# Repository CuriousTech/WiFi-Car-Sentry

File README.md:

# WiFi Car Sentry
Low power car monitor and control system  
  
Revision 2  
  
Using the ESP07, it connects with the home WiFi to report information on timer using DeepSleep.  Remember to remove the red LED on the ESP to reduce current.  This new revision uses a switching regulator for the lowest current possible.  It uses about 25mA on, and 39µA in sleep at 12.5V.  
  
I/O peripherals:  
  OLED (optional for temporary display)  
  DHT22 for temperature and Rh  
  0-17V analog voltage reading  
  2x 1-40V digital input (for sensing if something is on)  
  3x sink inputs (alarm or sensor)  
  3 sink outputs for controlling relays, etc (the bom has 7.6A MOSFETs)  
  Plus extra O/I for GPS or other sensors. The outputs can be used to switch them off for more power saving.

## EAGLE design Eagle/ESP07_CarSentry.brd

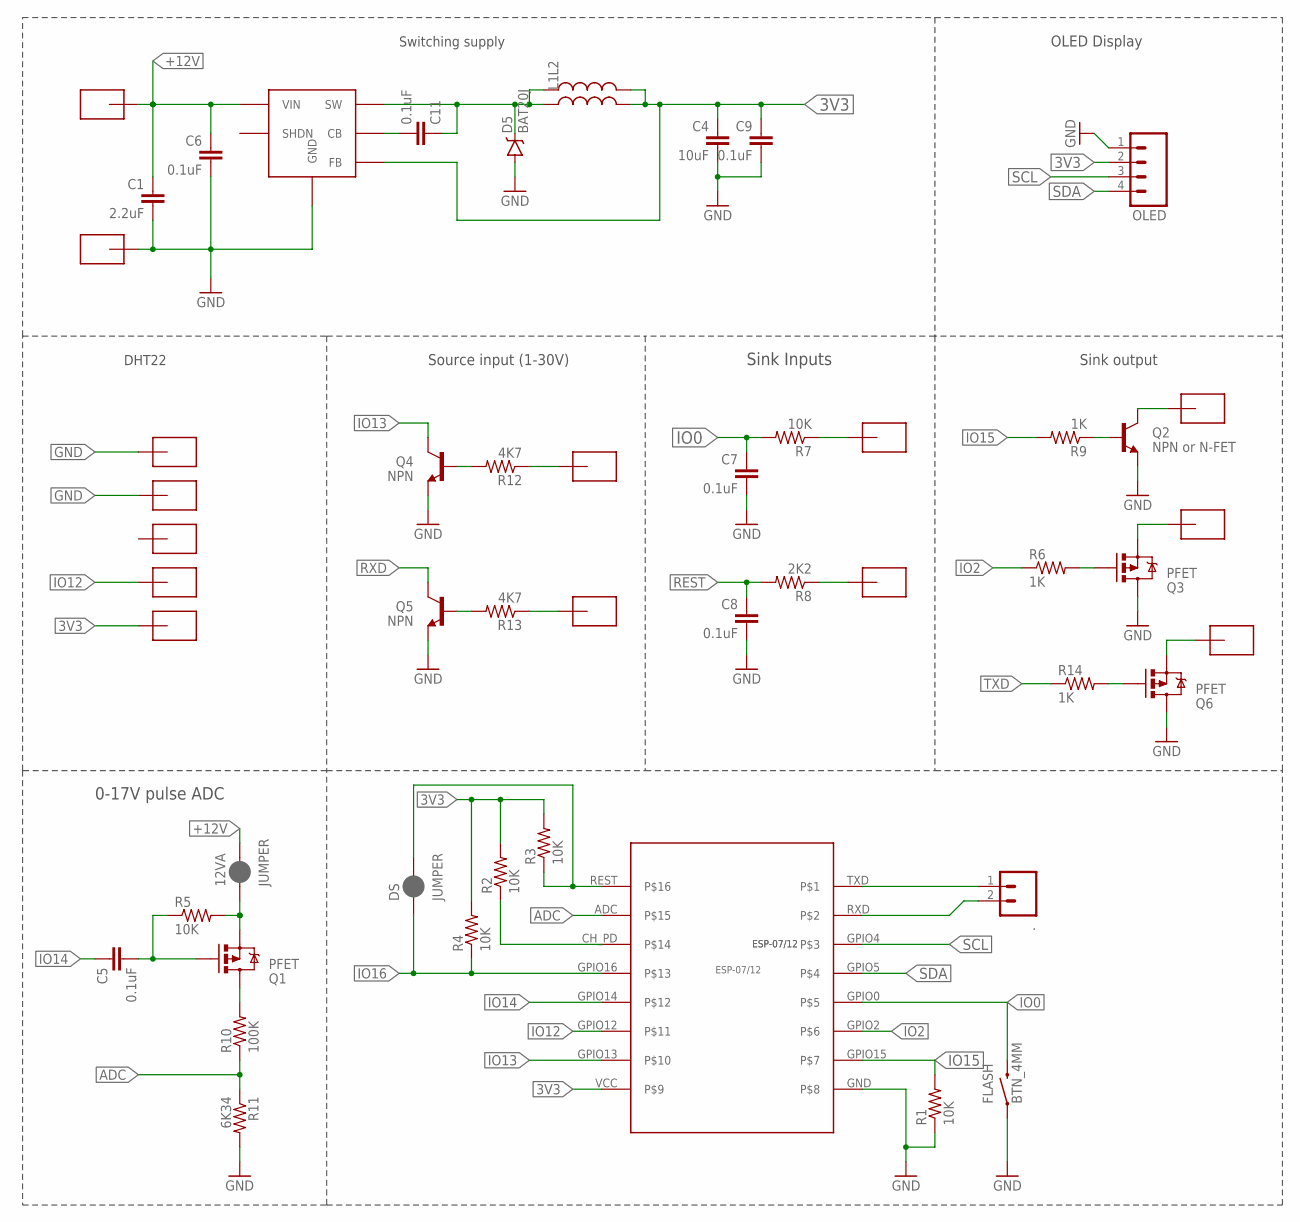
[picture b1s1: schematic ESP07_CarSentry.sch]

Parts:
12VA: JUMPER; PAD-JUMPER-2-NC_BY_PASTE_YES_SILK
.: M02PTH; 1X02
C1: 2.2uF; 0805-CAP
C4: 10uF; 0805-CAP
C5, C6, C7, C8, C9, C11: 0.1uF; 0805-CAP
D5: BAT20J; SOD-323
DS: JUMPER; PAD-JUMPER-2-NC_BY_PASTE_YES_SILK
FLASH: BTN_4MM
L1, L2: INDUCTOR0805; 0805
OLED: M04LOCK; 1X04_LOCK
Q1, Q3, Q6: PFET; SOT23-3
Q2: NPN or N-FET; SOT23-3
Q4, Q5: NPN; SOT23-3
R1, R2, R3, R4, R5, R7: 10K; 0805
R6, R9, R14: 1K; 0805
R8: 2K2; 0805
R10: 100K; 0805
R11: 6K34; 0805
R12, R13: 4K7; 0805
U$1: ESP-07/12
U$2, U$3, U$4, U$5, U$6, U$7, U$8, U$9, U$10, U$11, U$12, U$13, U$14, U$16: SMD-PAD1
VREG1: LMR16006YQ3DDCRQ1; SOT-23-6

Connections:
3V3: C4.1, C9.1, L1.2, L2.2, OLED.2, R2.2, R3.2, R4.2, U$1.VCC, U$4.>NAME, VREG1.3 (FB)
+12V: 12VA.2, C1.1, C6.1, U$16.>NAME, VREG1.5 (VIN)
ADC: R10.1, R11.1, U$1.ADC
ADCHI: 12VA.1, Q1.2 (S), R5.2
GND: C1.2, C4.2, C6.2, C7.2, C8.2, C9.2, D5.A, FLASH.1, OLED.1, Q2.2 (E), Q3.3 (D), Q4.2 (E), Q5.2 (E), Q6.3 (D), R1.1, R11.2, U$1.GND, U$6.>NAME, U$8.>NAME, U$11.>NAME, VREG1.2 (GND)
IO0: C7.1, FLASH.2, R7.2, U$1.GPIO0
IO2: R6.1, U$1.GPIO2
IO12: U$1.GPIO12, U$5.>NAME
IO13: Q4.3 (C), U$1.GPIO13
IO14: C5.1, U$1.GPIO14
IO15: R1.2, R9.2, U$1.GPIO15
IO16: DS.1, R4.1, U$1.GPIO16
unnamed: Q1.3 (D), R10.2
unnamed: Q3.1 (G), R6.2
unnamed: C5.2, Q1.1 (G), R5.1
unnamed: Q3.2 (S), U$9.>NAME
unnamed: R7.1, U$14.>NAME
unnamed: Q2.1 (B), R9.1
unnamed: Q2.3 (C), U$3.>NAME
unnamed: R8.1, U$12.>NAME
unnamed: Q4.1 (B), R12.2
unnamed: R12.1, U$2.>NAME
unnamed: R2.1, U$1.CH_PD
unnamed: Q5.1 (B), R13.2
unnamed: C11.1, D5.C, L1.1, L2.1, VREG1.6 (SW)
unnamed: C11.2, VREG1.1 (CB)
unnamed: R13.1, U$10.>NAME
unnamed: Q6.2 (S), U$13.>NAME
unnamed: Q6.1 (G), R14.2
REST: C8.1, DS.2, R3.1, R8.2, U$1.REST
RXD: ..2, Q5.3 (C), U$1.RXD
SCL: OLED.3, U$1.GPIO4
SDA: OLED.4, U$1.GPIO5
TXD: ..1, R14.1, U$1.TXD

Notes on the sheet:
0-17V pulse ADC
Sink Inputs
DHT22
Sink output
Source input (1-30V)
OLED Display
Switching supply

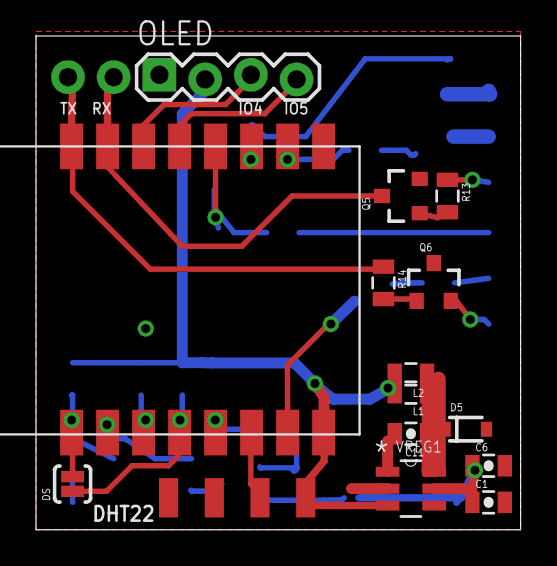
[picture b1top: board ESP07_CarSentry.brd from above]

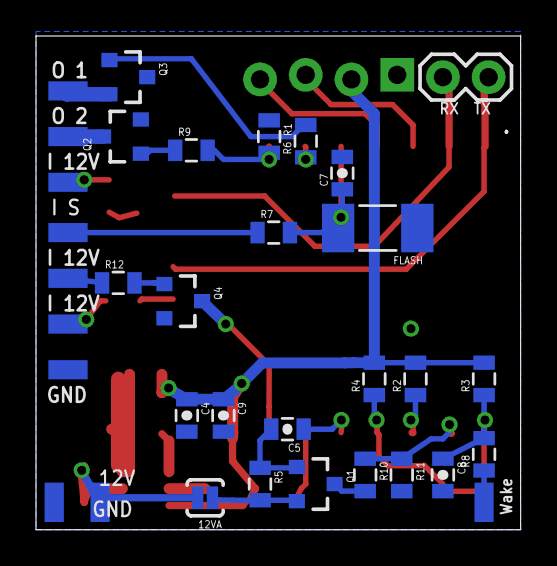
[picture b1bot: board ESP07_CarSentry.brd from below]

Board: 2 copper layers, 26.9 x 27.4 mm, 52 parts (34 on the bottom side), 34 nets.

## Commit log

2017-01-04 Monitor script
2017-01-12 Shutdown if configured AP not found
2017-01-12 Added server connect on wakeup
2017-01-18 Fixed key for updating
2017-01-18 Added SSID clear using flash button
2017-01-19 Faster shutdown when AP not in range
2017-01-20 Mistake on output function calls
2017-03-25 Switched Out 2 to PFET
2017-11-12 Updated for rev2
2017-11-12 rev 3
2017-11-12 rev 2 or something
2017-12-06 Update for 3 in / 3 out
2017-12-06 Updated for 3 in/3 out, pulse out, and OTA
2017-12-16 Chart, lon/lat display
2017-12-16 added stuff
2017-12-16 Connects to open wifi if possible
2017-12-16 Roaming and location
2018-05-01 Added favicon
2018-05-01 Removed printfs

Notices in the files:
parts and their libraries:
SparkFun-Connectors: Licensing: Creative Commons ShareAlike 4.0 International - https://creativecommons.org/licenses/by-sa/4.0
